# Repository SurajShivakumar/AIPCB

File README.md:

# AI PCB Copilot

Prompt an LLM to **read, review, simulate and edit KiCad projects** while you watch the changes in a browser.

It has two parts, both MCP servers, so any MCP client can use them (Claude Code, Claude Desktop, Cursor, opencode + a local model):

| Server | What it does |
|---|---|
| `kicad` | The editing engine: [mixelpixx/KiCAD-MCP-Server](https://github.com/mixelpixx/KiCAD-MCP-Server) v2.8.2 (MIT). ~240 tools: place, wire and label symbols; footprints; routing; exports; JLCPCB parts. |
| `copilot` | This repo. Checkpoints and undo, pin-level netlist diff, `verify_edit`, measured design review, SPICE on **LTspice and ngspice**, and a live browser view. |

See [PLAN.md](PLAN.md) for the design and roadmap.

## Setup (Windows)

You need KiCad 9 or 10, Node 18+, Python 3.11+ and git. LTspice is optional; ngspice comes with KiCad.

```powershell
powershell -ExecutionPolicy Bypass -File setup.ps1
```

The script clones the engine at its pinned tag, builds it against KiCad's Python, installs the copilot and runs the tests.

## Use it with Claude Code

```powershell
cd "AI PCB Generator"
claude          # approve the 'kicad' and 'copilot' servers the first time
```

Example prompts:

- *"Open workspace/fc and start the live view."*
- *"Review this board."* (uses the `review-schematic` skill)
- *"Add a 10k pull-up from nFAULT to 3.3V."* (uses `edit-schematic`: checkpoint → edit → verify → keep or undo)
- *"Simulate the BEMF dividers at 25.2 V and check the ADC pins stay under 3.3 V, on both LTspice and ngspice."* (uses `simulate`)
- *"Undo that."*

Work on copies. `sample_boards/` holds the originals; copy a board into `workspace/` and point the agent there.

### Seeing changes live

- **Browser (always):** `start_live_view` serves `http://127.0.0.1:8765`. It re-renders through `kicad-cli` within about a second of every save, circles the parts changed since the last checkpoint, and lists diffs, ERC counts, checkpoints and review findings. Clicking a finding jumps to its parts. The "Interactive" tab uses KiCanvas (alpha).
  - You can also run it without an agent: `.venv\Scripts\python -m copilot.viewer workspace\fc`
- **KiCad schematic editor:** KiCad 9/10 has no API for editing an open schematic, so the agent edits the file. `.mcp.json` turns on `KICAD_INTERACTIVE_SCHEMATIC`, which makes eeschema reload after each write. **Save your own edits before asking the agent to edit.** It will never auto-confirm a "discard changes" dialog.
- **KiCad PCB editor:** truly live (undoable) when the board is open in pcbnew with *Preferences → Plugins → Enable IPC API server* on.

## Copilot tools

| Tool | Purpose |
|---|---|
| `project_status`, `start_live_view` | Session setup |
| `checkpoint`, `list_checkpoints`, `undo`, `restore_checkpoint` | Snapshots in a shadow git repo at `<project>/.copilot/git`. This never touches your own git. |
| `netlist_diff`, `verify_edit` | Pin-level diff (name-independent), ERC new/resolved, flags parts touched outside the plan and unplanned net merges |
| `get_netlist` | Ground-truth connectivity from `kicad-cli` |
| `review_design` | ERC, optional DRC with schematic parity, netlist rules, fab-rule checks. Writes `.copilot/review.md` |
| `spice_check`, `spice_build_deck`, `spice_run`, `spice_simulators` | Decks from the schematic; LTspice / ngspice / both with a cross-check; pass/fail assertions |
| `pin_positions`, `connect_power`, `draw_wire`, `tidy_schematic` | Edits in hand-drawn style: power symbols instead of text labels; straight on-grid wires with junction dots; grid snap and text de-overlap; saves byte-identical to KiCad's own file format |

**Build + route the V2 ESC in one go** (repo root, PowerShell):

```powershell
.\autopcb_run                 # build, route, finish, stitch, clean up, DRC - live progress dashboard in this window
.\autopcb_run --skip-build    # keep the current placement, just re-route
.\autopcb_logs                # watch a run from a second window (stays open; Ctrl+C to close; --once / --log)
.\autopcb_run --docker        # same run inside the autopcb-kicad container: nothing opens on the desktop
```

Everything is also logged to `logs/autopcb.log`.

**Each run ends with design checks and a commit.** After DRC, the pipeline:
1. runs `tools/esc_checks.py`. This covers what DRC can't see:
   - switching-loop cap distance
   - charge-pump caps
   - gate-drive length
   - signals crossing a phase pour
   - vias in pads
   - ground return under the crystal/MCU
   - mounting holes
   - 3D models
2. renders every copper layer and the 3D top and bottom views into `workspace/esc_v2/review/`.
3. commits the KiCad project and the review folder to the `esc-v2` branch of [Autonomous-Flight-Team/ESC_PCB](https://github.com/Autonomous-Flight-Team/ESC_PCB), using `tools/publish_branch.py`. Pass `--no-publish` to skip the commit.

**No windows.**
- Every tool starts its child processes hidden (`tools/_quiet.py`).
- `--docker` runs the whole build and route in Linux. The image is `docker/Dockerfile`: KiCad 9.0.6, numpy, numba and Pillow. It is built on first use, and the Docker engine is started headless with `docker desktop start`.
- The image has no 3D model library, so the 3D views and the git push run on Windows afterwards, also hidden.
- KiCad paths come from `tools/_env.py`. Override them with `AUTOPCB_KPY`, `KICAD_CLI` and `KICAD_SHARE`.

**Board scripts** (`tools/`, run with KiCad's Python at `vendor/KiCAD-MCP-Server/venv/Scripts/python.exe`):

| Script | Purpose |
|---|---|
| `sync_board.py` | "Update PCB from Schematic", scripted: adds and moves footprints, reloads changed library footprints, renames nets on existing copper, locks existing routing |
| `route_board.py` | Freerouting autoroute. Plane nets are left to pours. `--keep` adds routes without touching existing ones. Picks a Java new enough for Freerouting. |
| `finish_route.py` + `maze_route.py` | Routes exactly what KiCad's ratsnest still reports missing, with a clearance-aware 2-layer maze router that respects edge and top-layer keep-outs |
| `prune_tracks.py`, `stitch_islands.py`, `silk_fix.py` | Remove dangling stubs and vias; stitch pour islands; move reference designators off pads and other silkscreen |
| `build_esc_v2.py` | Generates the 4-layer V2 ESC board: placement, stackup, zones, via fields, top-layer signal keep-out |
| `drc_summary.py`, `jlc_lookup.py` | Compact DRC report; JLCPCB/LCSC part lookup (basic/extended, stock, price) |

**Review rules:**
- Errors:
  - capacitors wired only to each other (a missing supply label)
  - missing decoupling on IC supply pins
  - USB-C CC pins without pull-downs
  - unannotated parts, missing footprints
  - schematic/PCB disagreement
  - tracks or vias below the fab's limits
- Warnings:
  - missing pull-ups on I2C / open-drain lines
  - crystals without load caps
  - LEDs without a resistor
  - look-alike net names that aren't connected
  - single-pin labelled nets
  - sheets pointing at missing files
  - symbols off the page
  - project DRC limits looser than the fab
- Fab profiles live in [fab-profiles/](fab-profiles/).

## Other clients

Point any MCP client at the same two commands. The paths are relative to this folder; use absolute paths if the client starts elsewhere.

- engine: `node vendor/KiCAD-MCP-Server/dist/index.js`
- copilot: `.venv/Scripts/python.exe -m copilot.server`

**Free / local:** [opencode](https://opencode.ai) with Ollama or LM Studio. Use a model with solid tool calling (Qwen3-Coder class or bigger); small models struggle with long edit chains. The engine ships `setup-windows-opencode.ps1` for its half.

## Tests

```powershell
.venv\Scripts\python -m pytest
```

The tests cover the netlist diff, value parsing, an RC transient on both simulators with a cross-check, and the review rules against netlists from the sample boards.

## Known limits

- **Schematic edits are file edits.** "Live" in eeschema means it reloads after each write.
- **The engine's own net listing misses power-symbol nets.** The copilot uses `kicad-cli` as ground truth.
- **The engine can report a connection as done when it isn't.** `verify_edit` catches this, which is why the edit loop always verifies.
- **SPICE models R/C/L/ferrite/diode/zener/LED automatically.** ICs need a `loads` stand-in or a `models` line.
- **DRC takes about 1 minute on a 4-layer board,** so it's opt-in.

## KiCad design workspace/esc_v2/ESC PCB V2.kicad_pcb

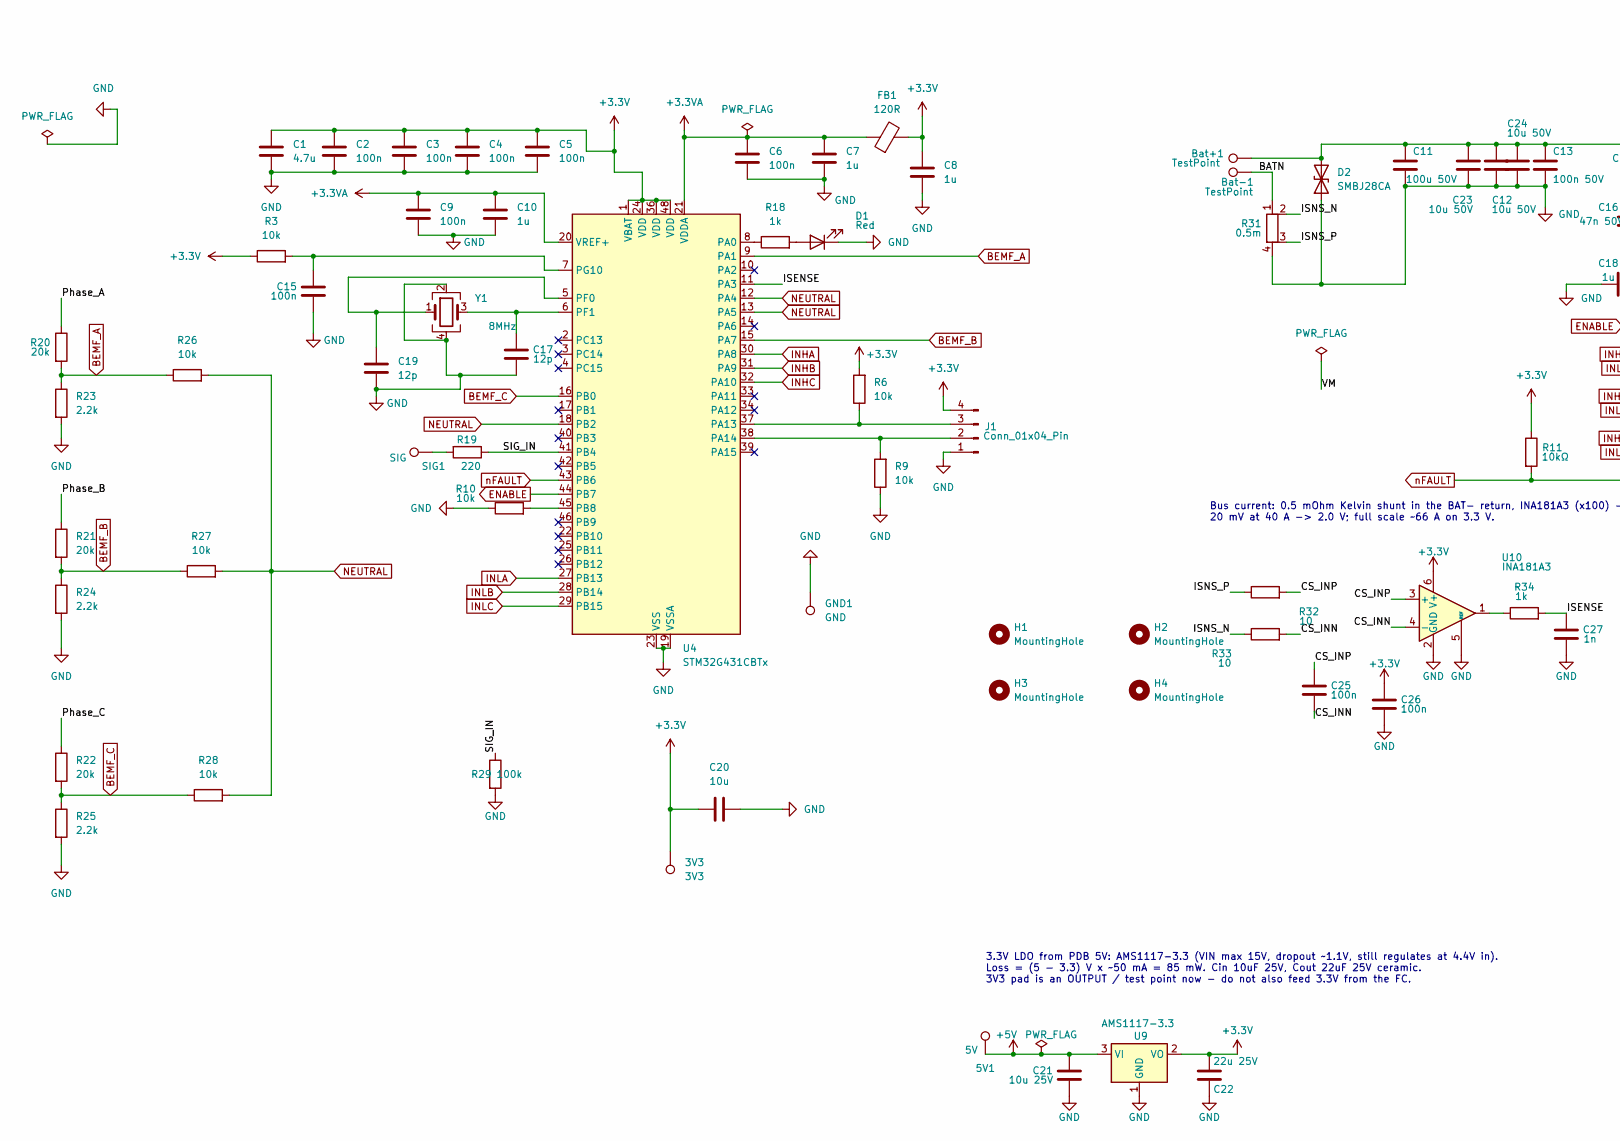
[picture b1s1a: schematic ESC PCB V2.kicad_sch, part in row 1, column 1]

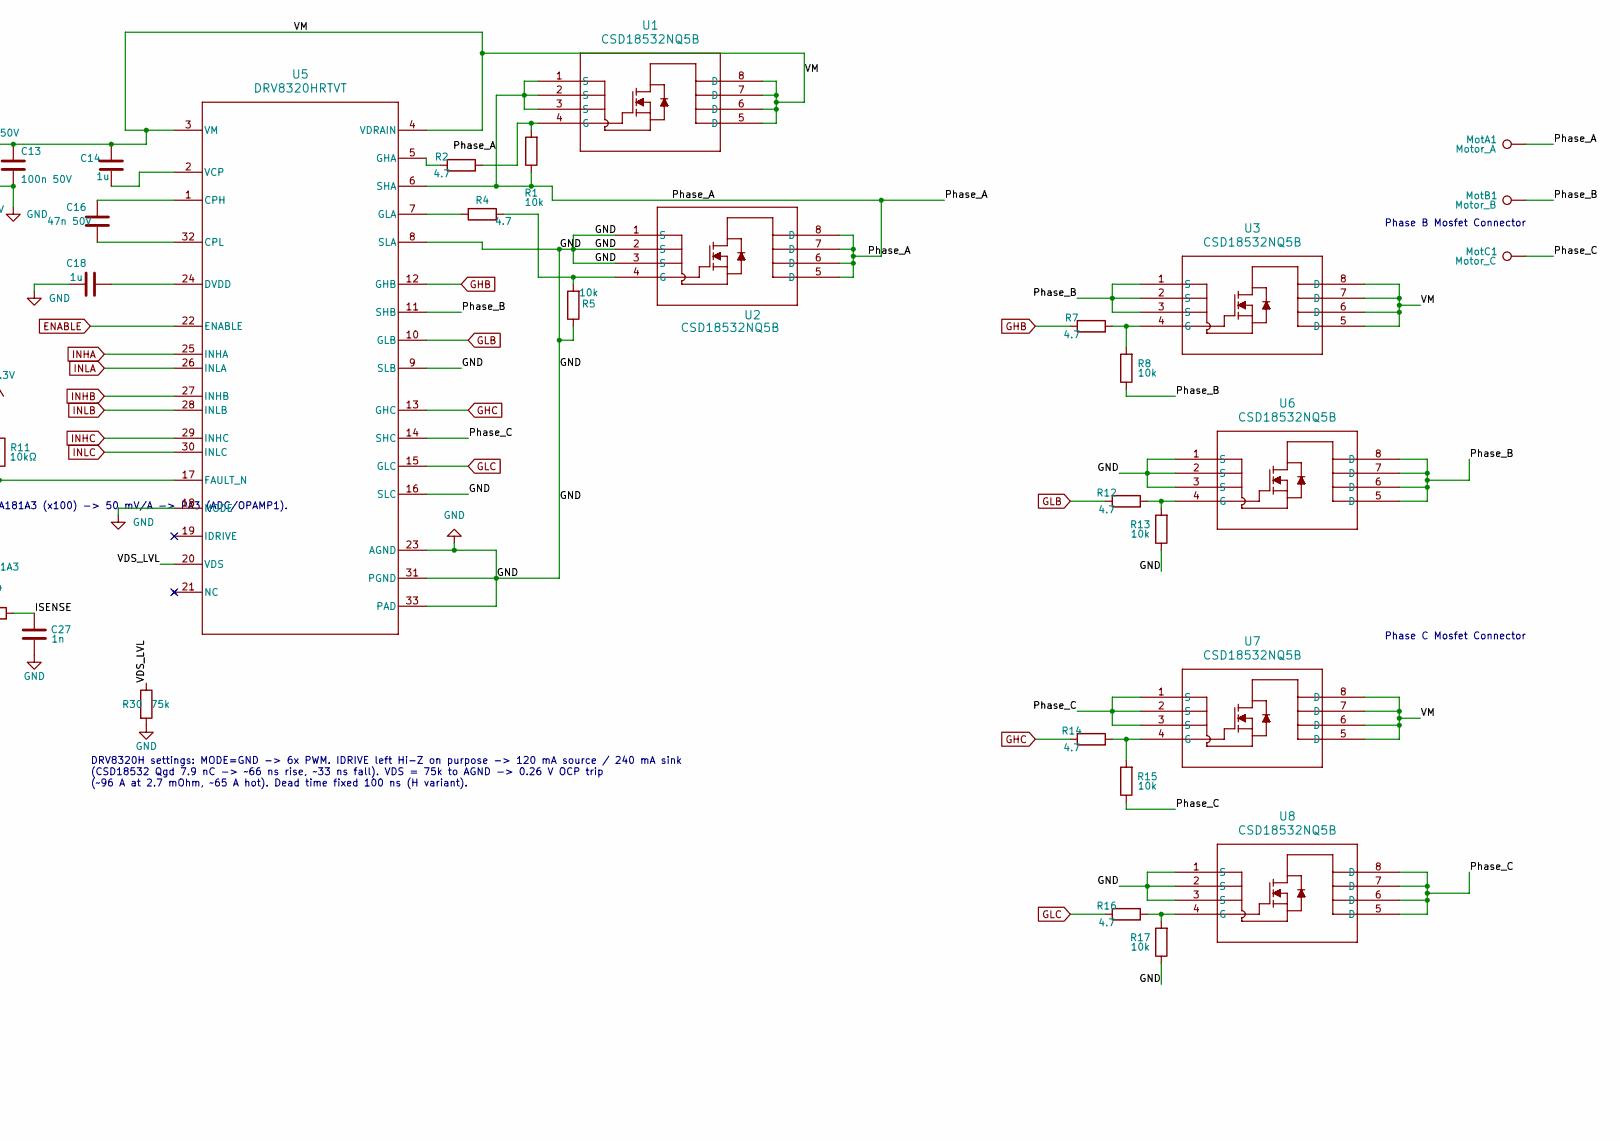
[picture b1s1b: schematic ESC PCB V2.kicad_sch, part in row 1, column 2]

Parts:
3V3: 3V3; SolderWirePad_1x01_SMD_2x4mm
5V1: 5V; SolderWirePad_1x01_SMD_2x4mm
Bat+1: TestPoint; SolderWirePad_1x01_SMD_5x10mm
Bat-1: TestPoint; SolderWirePad_1x01_SMD_5x10mm
C1: 4.7u; C_0603_1608Metric; MPN CL10A475KO8NNNC; LCSC C19666
C2, C3, C4, C5, C6, C9, C15, C25, C26: 100n; C_0603_1608Metric; MPN CC0603KRX7R9BB104; LCSC C14663
C7, C8, C10, C14, C18: 1u; C_0603_1608Metric; MPN CL10A105KB8NNNC; LCSC C15849
C11: 100u 50V; CP_Elec_10x10.5; MPN EEE-FK1H101P
C12, C23, C24: 10u 50V; C_1210_3225Metric; MPN GRM32ER61H106KA12L; LCSC C412253
C13: 100n 50V; C_0603_1608Metric; MPN CC0603KRX7R9BB104; LCSC C14663
C16: 47n 50V; C_0603_1608Metric; MPN CL10B473KB8NNNC; LCSC C1622
C17, C19: 12p; C_0603_1608Metric; MPN CL10C120JB8NNNC; LCSC C38523
C20: 10u; C_0603_1608Metric; MPN CL10A106KP8NNNC; LCSC C19702
C21: 10u 25V; C_0603_1608Metric; MPN CL10A106MA8NRNC; LCSC C96446
C22: 22u 25V; C_0805_2012Metric; MPN CL21A226MAQNNNE; LCSC C45783
C27: 1n; C_0603_1608Metric; MPN CL10B102KB8NNNC; LCSC C1588
D1: Red; LED_0603_1608Metric; MPN KT-0603R; LCSC C2286
D2: SMBJ28CA; SMBJSeries_LTF; MPN SMBJ28CA; LCSC C19077583
FB1: 120R; L_0603_1608Metric; MPN BLM18PG121SN1D; LCSC C14709
GND1: GND; SolderWirePad_1x01_SMD_2x4mm
H1, H2, H3, H4: MountingHole; MountingHole_3.2mm_M3
J1: Conn_01x04_Pin; JST_SH_SM04B-SRSS-TB_1x04-1MP_P1.00mm_Horizontal; MPN SM04B-SRSS-TB(LF)(SN); LCSC C160404
MotA1: Motor_A; SolderWirePad_1x01_SMD_5x10mm
MotB1: Motor_B; SolderWirePad_1x01_SMD_5x10mm
MotC1: Motor_C; SolderWirePad_1x01_SMD_5x10mm
R1, R3, R5, R6, R8, R9, R10, R13, R15, R17, R26, R27, R28: 10k; R_0603_1608Metric; MPN 0603WAF1002T5E; LCSC C25804
R2, R4, R7, R12, R14, R16: 4.7; R_0603_1608Metric; MPN 0603WAF470KT5E; LCSC C23164
R11: 10kΩ; R_0603_1608Metric; MPN 0603WAF1002T5E; LCSC C25804
R18, R34: 1k; R_0603_1608Metric; MPN 0603WAF1001T5E; LCSC C21190
R19: 220; R_0603_1608Metric; MPN 0603WAF2200T5E; LCSC C22962
R20, R21, R22: 20k; R_0603_1608Metric; MPN 0603WAF2002T5E; LCSC C4184
R23, R24, R25: 2.2k; R_0603_1608Metric; MPN 0603WAF2201T5E; LCSC C4190
R29: 100k; R_0603_1608Metric; MPN 0603WAF1003T5E; LCSC C25803
R30: 75k; R_0603_1608Metric; MPN 0603WAF7502T5E; LCSC C23242
R31: 0.5m; R_Shunt_2512_Kelvin; MPN RLM25FEGMR50M; LCSC C710260
R32, R33: 10; R_0603_1608Metric; MPN 0603WAF100JT5E; LCSC C22859
SIG1: SIG; SolderWirePad_1x01_SMD_2x4mm
U1, U2, U3, U6, U7, U8: CSD18532NQ5B; DNK8_TEX; MPN CSD18532NQ5B
U4: STM32G431CBTx; LQFP-48_7x7mm_P0.5mm; MPN STM32G431CBT6; LCSC C529355
U5: DRV8320HRTVT; RTV0032E; MPN DRV8320HRTVR; LCSC C701782
U9: AMS1117-3.3; SOT-223-3_TabPin2; MPN AMS1117-3.3; LCSC C6186
U10: INA181A3; SOT-23-6; MPN INA181A3IDBVR; LCSC C2652255
Y1: 8MHz; Crystal_SMD_3225-4Pin_3.2x2.5mm; MPN TAXM8M4RDBCCT2T; LCSC C400090

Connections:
+3.3V: 3V3.1, C1.1, C2.1, C3.1, C4.1, C5.1, C8.1, C20.1, C22.1, C26.1, FB1.2, J1.4, R3.1, R6.2, R11.1, U4.1 (VBAT), U4.24 (VDD), U4.36 (VDD), U4.48 (VDD), U9.2 (VO), U10.6 (V+)
+3.3VA: C6.1, C7.1, C9.1, C10.1, FB1.1, U4.20 (VREF+), U4.21 (VDDA)
+5V: 5V1.1, C21.1, U9.3 (VI)
/BATN: Bat-1.1, R31.1
/CS_INN: C25.2, R33.2, U10.4 (-)
/CS_INP: C25.1, R32.2, U10.3 (+)
/ISENSE: C27.1, R34.2, U4.11 (PA3)
/ISNS_N: R31.2, R33.1
/ISNS_P: R31.3, R32.1
/Phase_A: MotA1.1, R1.1, R20.1, U1.1 (S), U1.2 (S), U1.3 (S), U2.5 (D), U2.6 (D), U2.7 (D), U2.8 (D), U5.6 (SHA)
/Phase_B: MotB1.1, R8.1, R21.1, U3.1 (S), U3.2 (S), U3.3 (S), U5.11 (SHB), U6.5 (D), U6.6 (D), U6.7 (D), U6.8 (D)
/Phase_C: MotC1.1, R15.1, R22.1, U5.14 (SHC), U7.1 (S), U7.2 (S), U7.3 (S), U8.5 (D), U8.6 (D), U8.7 (D), U8.8 (D)
/SIG_IN: R19.1, R29.1, U4.41 (PB4)
/VDS_LVL: R30.1, U5.20 (VDS)
/VM: Bat+1.1, C11.1, C12.1, C13.1, C14.2, C23.1, C24.1, D2.2 (A2), U1.5 (D), U1.6 (D), U1.7 (D), U1.8 (D), U3.5 (D), U3.6 (D), U3.7 (D), U3.8 (D), U5.3 (VM), U5.4 (VDRAIN), U7.5 (D), U7.6 (D), U7.7 (D), U7.8 (D)
BEMF_A: R20.2, R23.1, R26.1, U4.9 (PA1)
BEMF_B: R21.2, R24.1, R27.1, U4.15 (PA7)
BEMF_C: R22.2, R25.1, R28.1, U4.16 (PB0)
ENABLE: U4.44 (PB7), U5.22 (ENABLE)
GHB: R7.1, U5.12 (GHB)
GHC: R14.1, U5.13 (GHC)
GLB: R12.1, U5.10 (GLB)
GLC: R16.1, U5.15 (GLC)
GND: C1.2, C2.2, C3.2, C4.2, C5.2, C6.2, C7.2, C8.2, C9.2, C10.2, C11.2, C12.2, C13.2, C15.2, C17.2, C18.1, C19.2, C20.2, C21.2, C22.2, C23.2, C24.2, C26.2, C27.2, D1.1 (K), D2.1 (A1), GND1.1, J1.1, R5.1, R9.1, R10.1, R13.1, R17.1, R23.2, R24.2, R25.2, R29.2, R30.2, R31.4, U2.1 (S), U2.2 (S), U2.3 (S), U4.19 (VSSA), U4.23 (VSS), U4.35 (VSS), U4.47 (VSS), U5.8 (SLA), U5.9 (SLB), U5.16 (SLC), U5.18 (MODE), U5.23 (AGND), U5.31 (PGND), U5.33 (PAD), U6.1 (S), U6.2 (S), U6.3 (S), U8.1 (S), U8.2 (S), U8.3 (S), U9.1 (GND), U10.2 (GND), U10.5 (REF), Y1.2, Y1.4
INHA: U4.30 (PA8), U5.25 (INHA)
INHB: U4.31 (PA9), U5.27 (INHB)
INHC: U4.32 (PA10), U5.29 (INHC)
INLA: U4.27 (PB13), U5.26 (INLA)
INLB: U4.28 (PB14), U5.28 (INLB)
INLC: U4.29 (PB15), U5.30 (INLC)
NEUTRAL: R26.2, R27.2, R28.2, U4.12 (PA4), U4.13 (PA5), U4.18 (PB2)
unnamed: D1.2 (A), R18.2
unnamed: J1.2, R9.2, U4.38 (PA14)
unnamed: J1.3, R6.1, U4.37 (PA13)
unnamed: R19.2, SIG1.1
unnamed: R34.1, U10.1
unnamed: R1.2, R2.2, U1.4 (G)
unnamed: R4.2, R5.2, U2.4 (G)
unnamed: R7.2, R8.2, U3.4 (G)
unnamed: R18.1, U4.8 (PA0)
unnamed: R10.2, U4.45 (PB8)
unnamed: C19.1, U4.5 (PF0), Y1.1
unnamed: C17.1, U4.6 (PF1), Y1.3
unnamed: C15.1, R3.2, U4.7 (PG10)
unnamed: C16.2, U5.1 (CPH)
unnamed: C16.1, U5.32 (CPL)
unnamed: C18.2, U5.24 (DVDD)
unnamed: R2.1, U5.5 (GHA)
unnamed: R4.1, U5.7 (GLA)
unnamed: C14.1, U5.2 (VCP)
unnamed: R12.2, R13.2, U6.4 (G)
unnamed: R14.2, R15.2, U7.4 (G)
unnamed: R16.2, R17.2, U8.4 (G)
nFAULT: R11.2, U4.43 (PB6), U5.17 (FAULT_N)

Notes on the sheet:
3.3V LDO from PDB 5V: AMS1117-3.3 (VIN max 15V, dropout ~1.1V, still regulates at 4.4V in). Loss = (5 - 3.3) V x ~50 mA = 85 mW. Cin 10uF 25V, Cout 22uF 25V ceramic. 3V3 pad is an OUTPUT / test point now - do not also feed 3.3V from the FC.
DRV8320H settings: MODE=GND -> 6x PWM. IDRIVE left Hi-Z on purpose -> 120 mA source / 240 mA sink (CSD18532 Qgd 7.9 nC -> ~66 ns rise, ~33 ns fall). VDS = 75k to AGND -> 0.26 V OCP trip (~96 A at 2.7 mOhm, ~65 A hot). Dead time fixed 100 ns (H variant).
Phase C Mosfet Connector
Phase B Mosfet Connector
Bus current: 0.5 mOhm Kelvin shunt in the BAT- return, INA181A3 (x100) -> 50 mV/A -> PA3 (ADC/OPAMP1). 20 mV at 40 A -> 2.0 V; full scale ~66 A on 3.3 V.

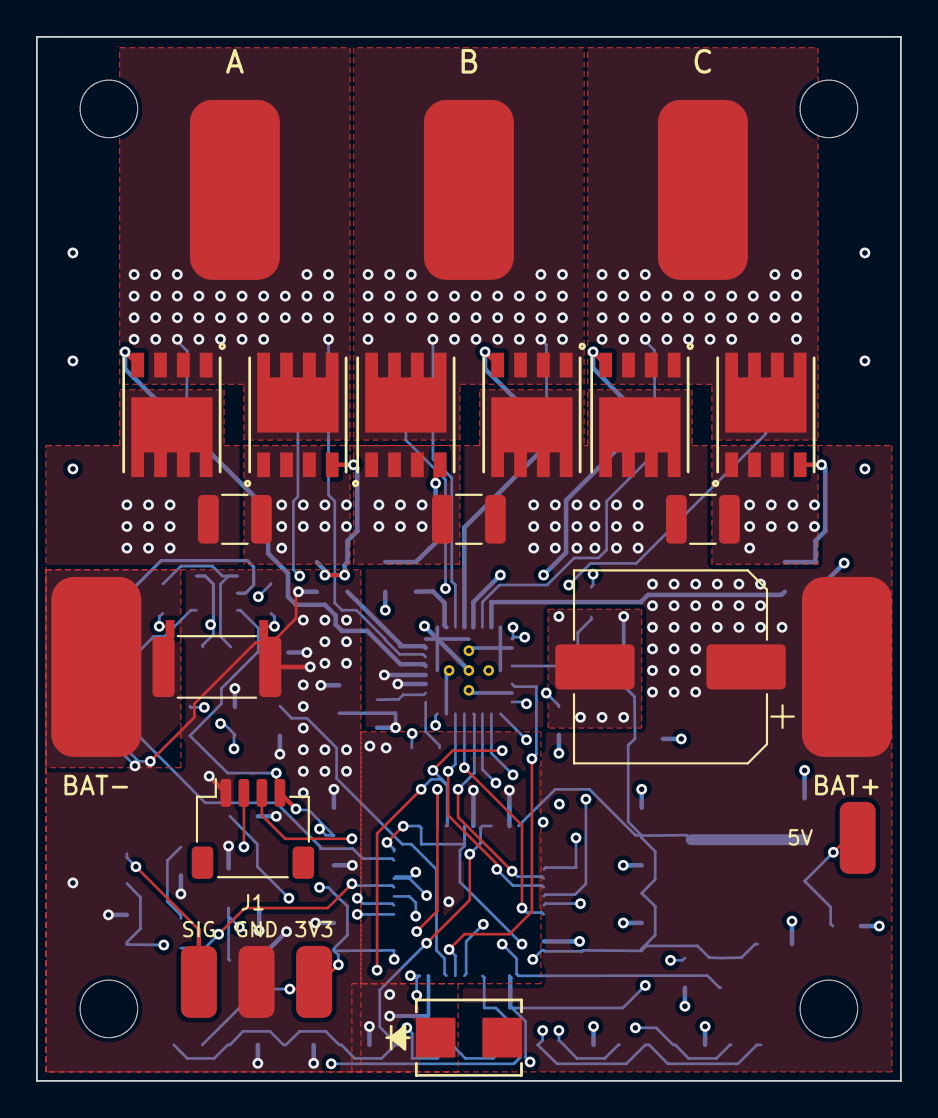
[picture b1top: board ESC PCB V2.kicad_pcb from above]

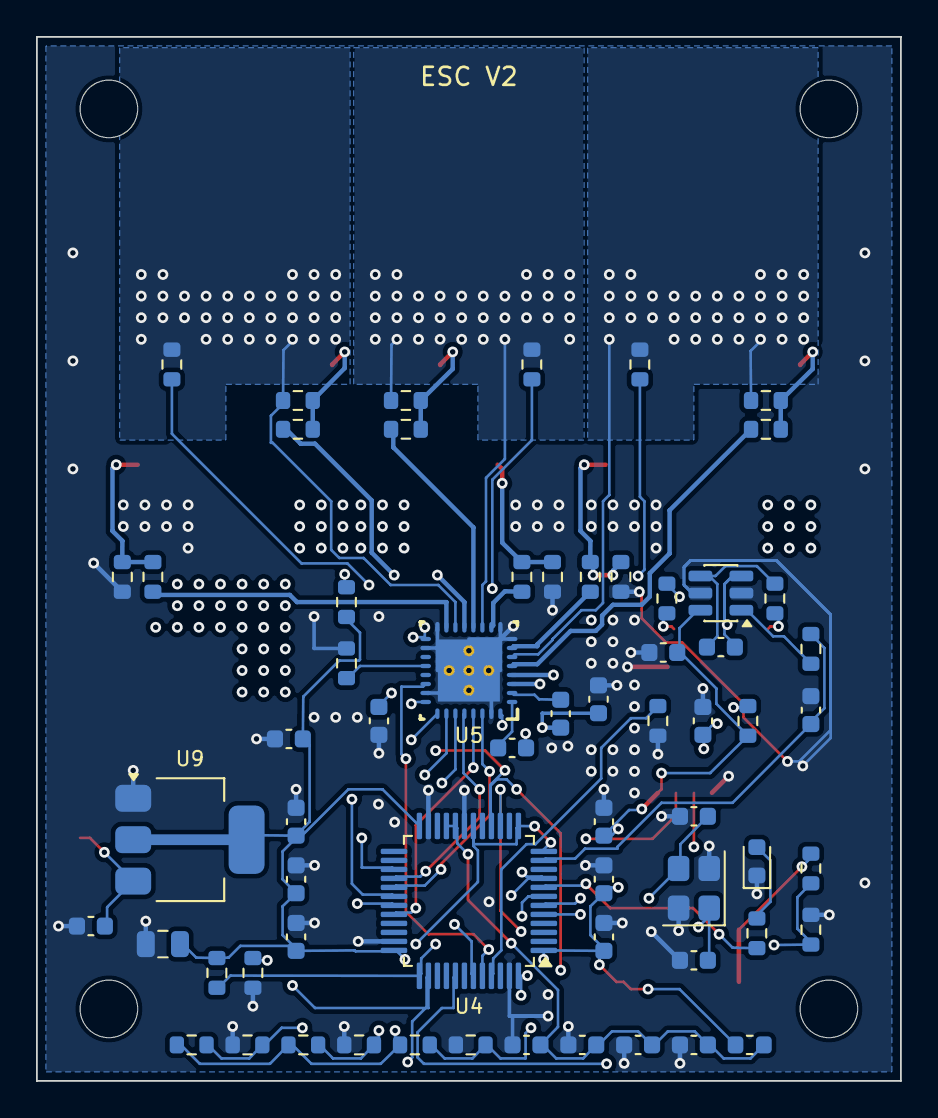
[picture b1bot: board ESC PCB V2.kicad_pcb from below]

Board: 4 copper layers, 48.0 x 58.0 mm, 89 parts (63 on the bottom side), 54 nets.

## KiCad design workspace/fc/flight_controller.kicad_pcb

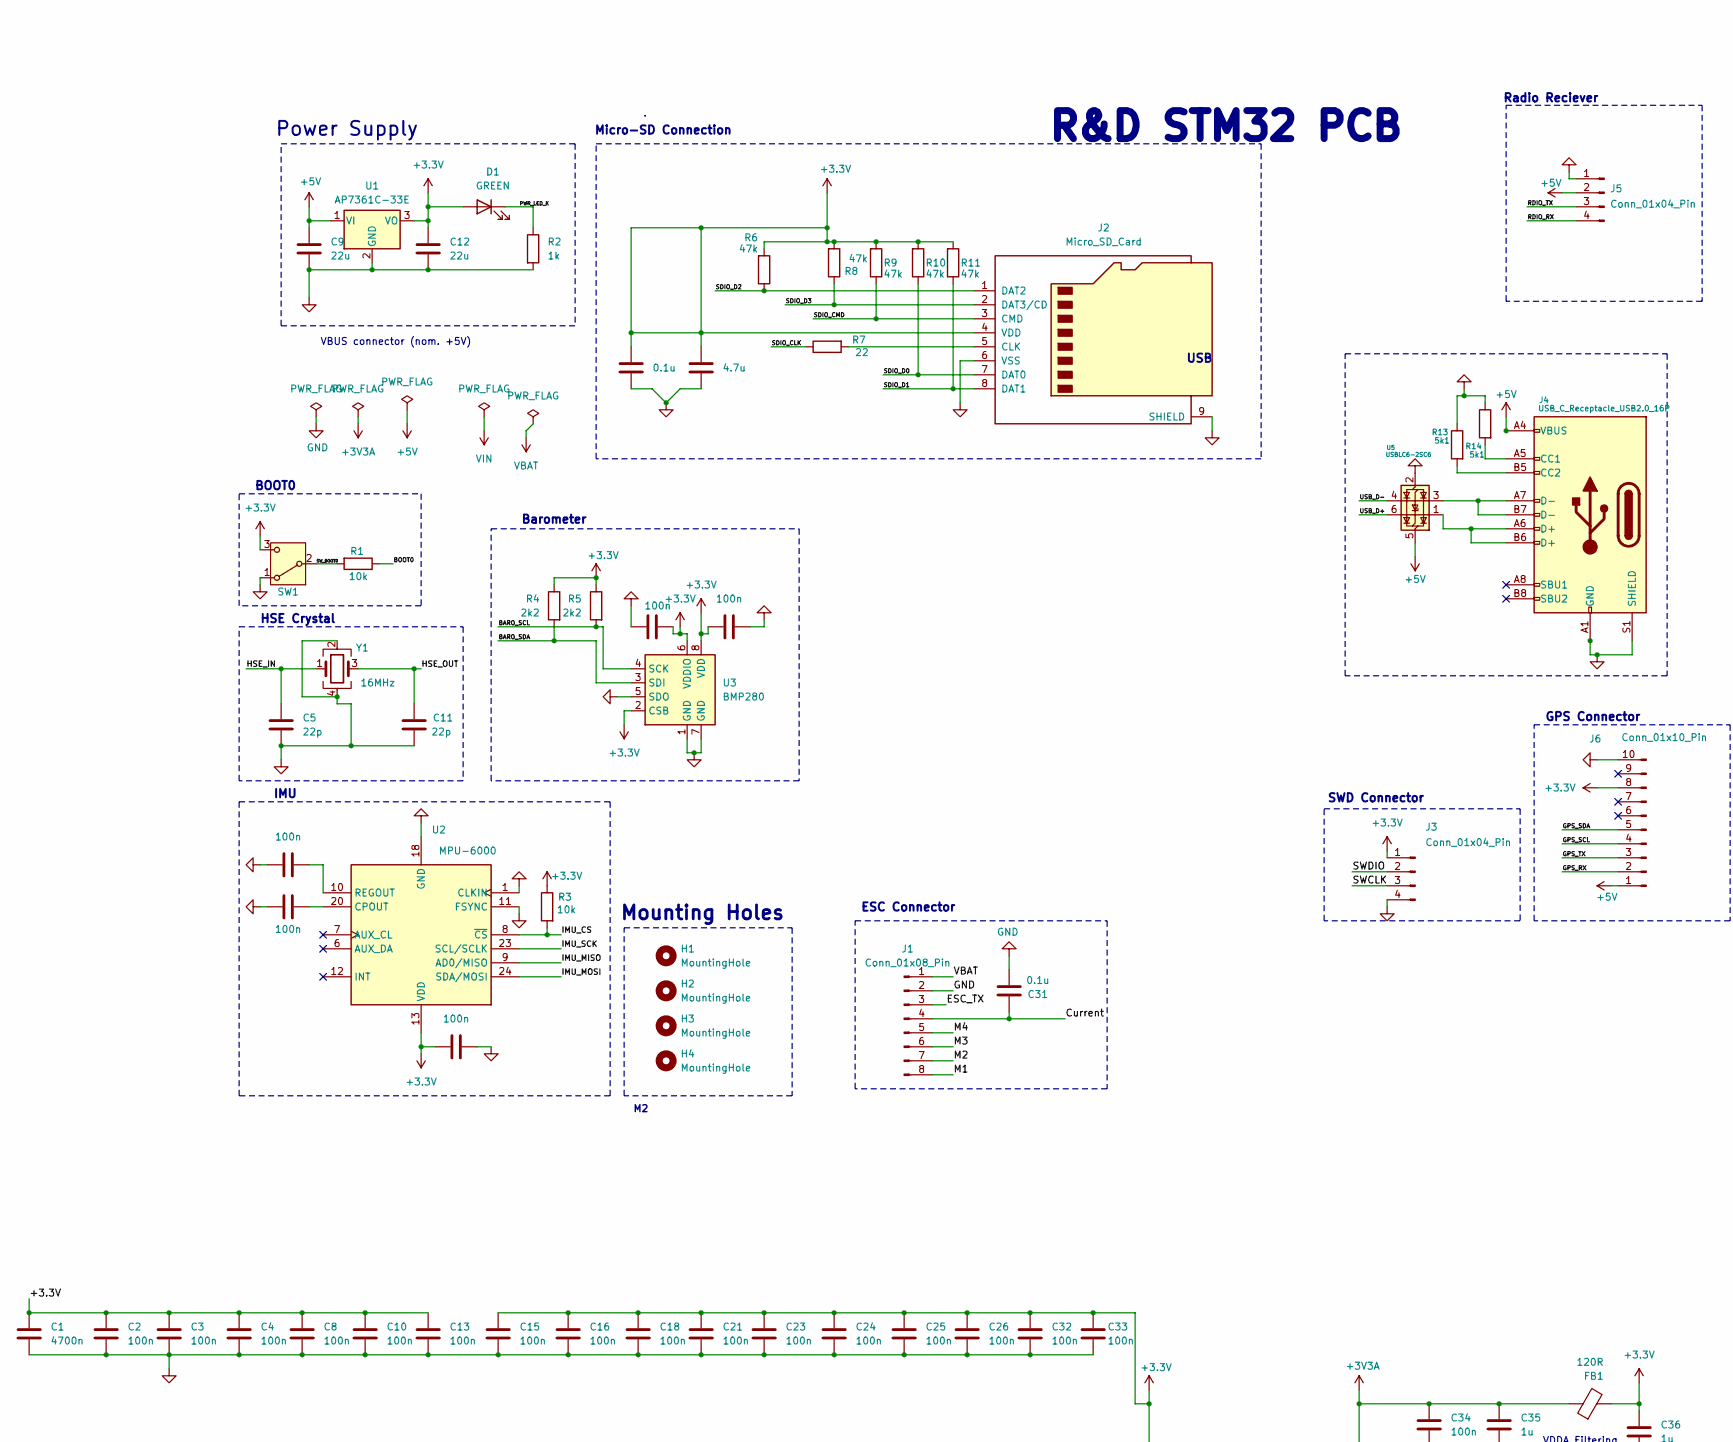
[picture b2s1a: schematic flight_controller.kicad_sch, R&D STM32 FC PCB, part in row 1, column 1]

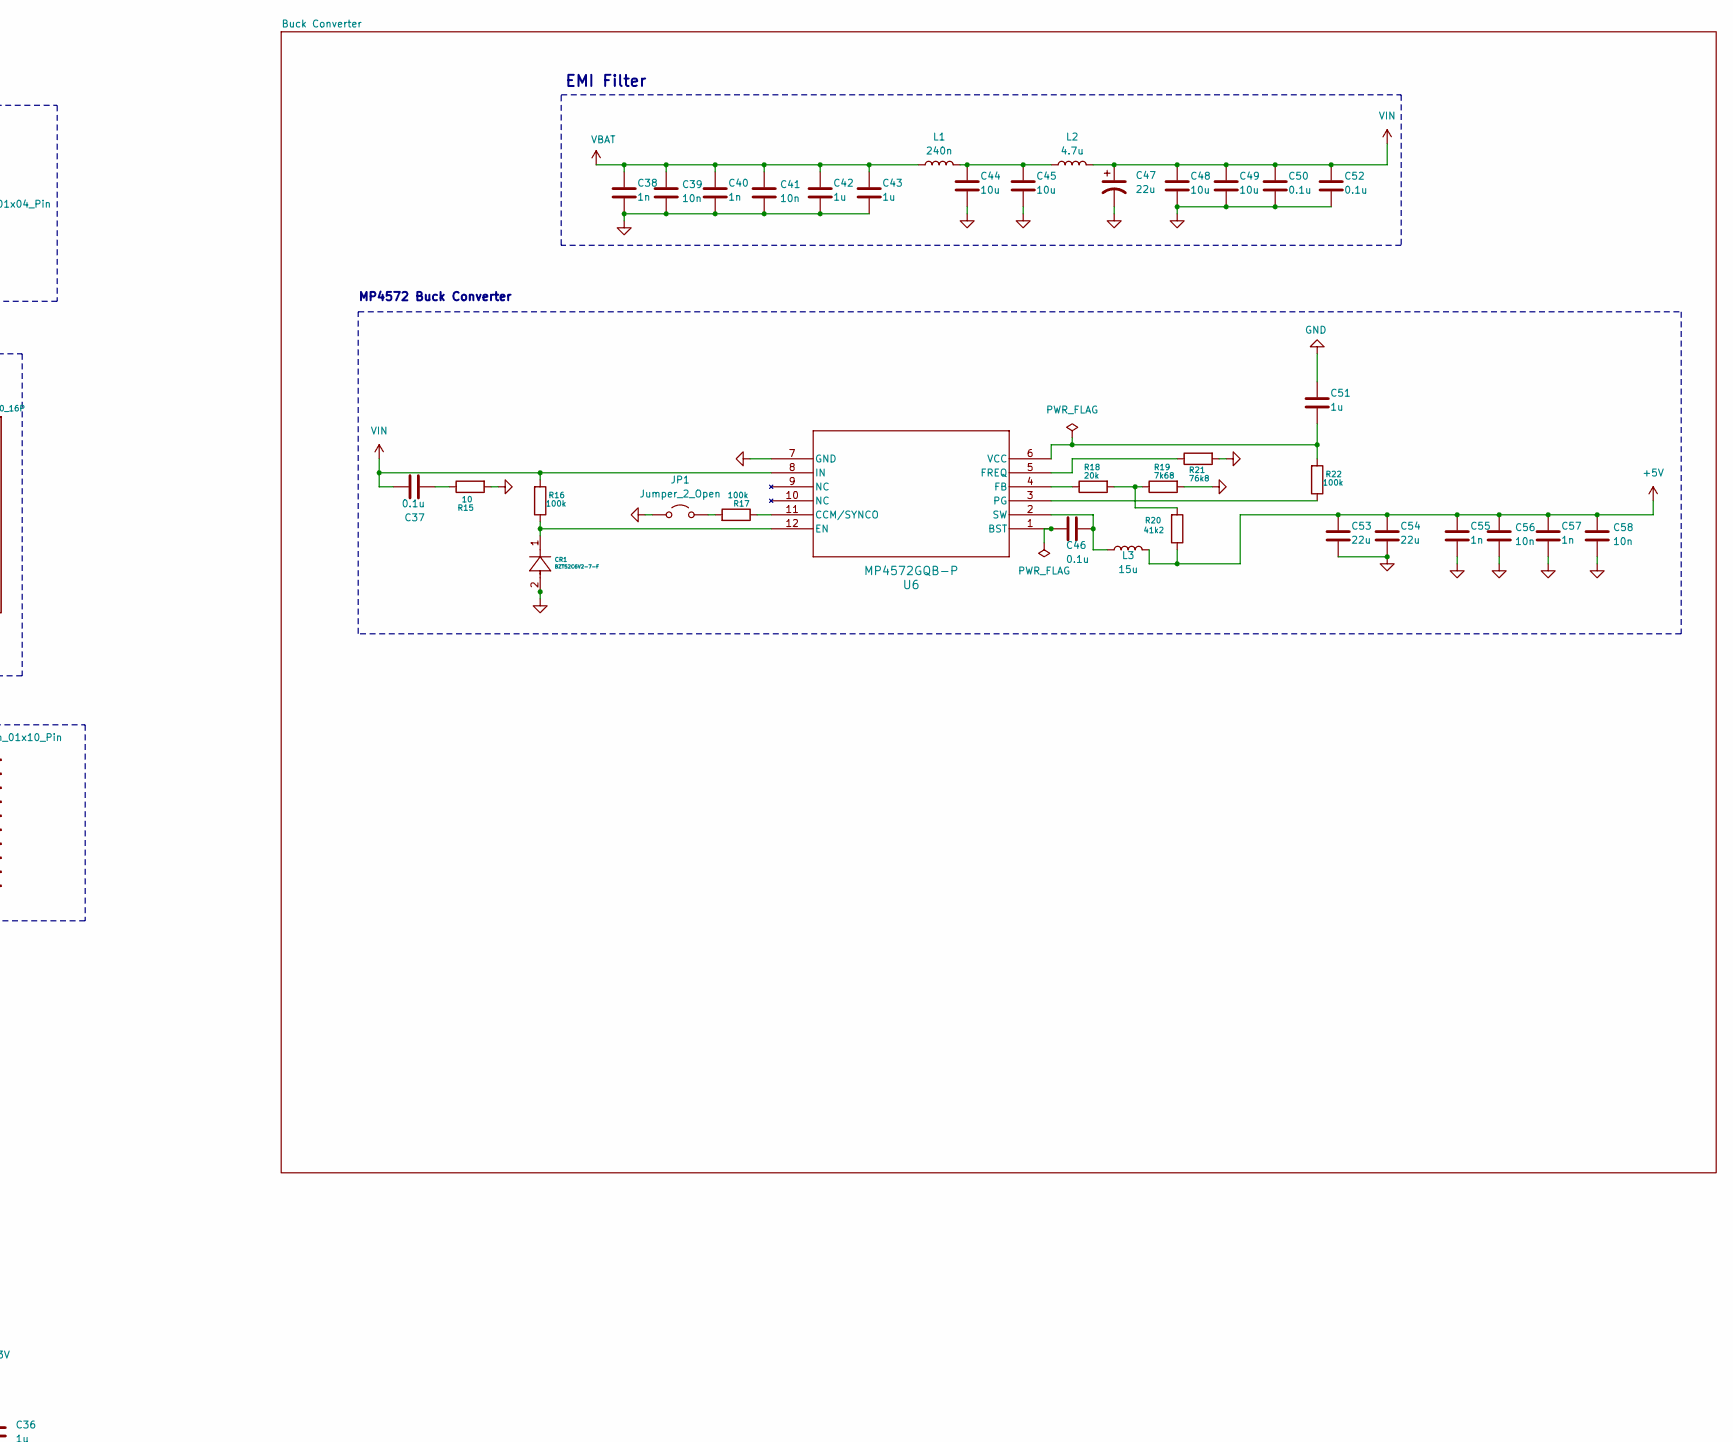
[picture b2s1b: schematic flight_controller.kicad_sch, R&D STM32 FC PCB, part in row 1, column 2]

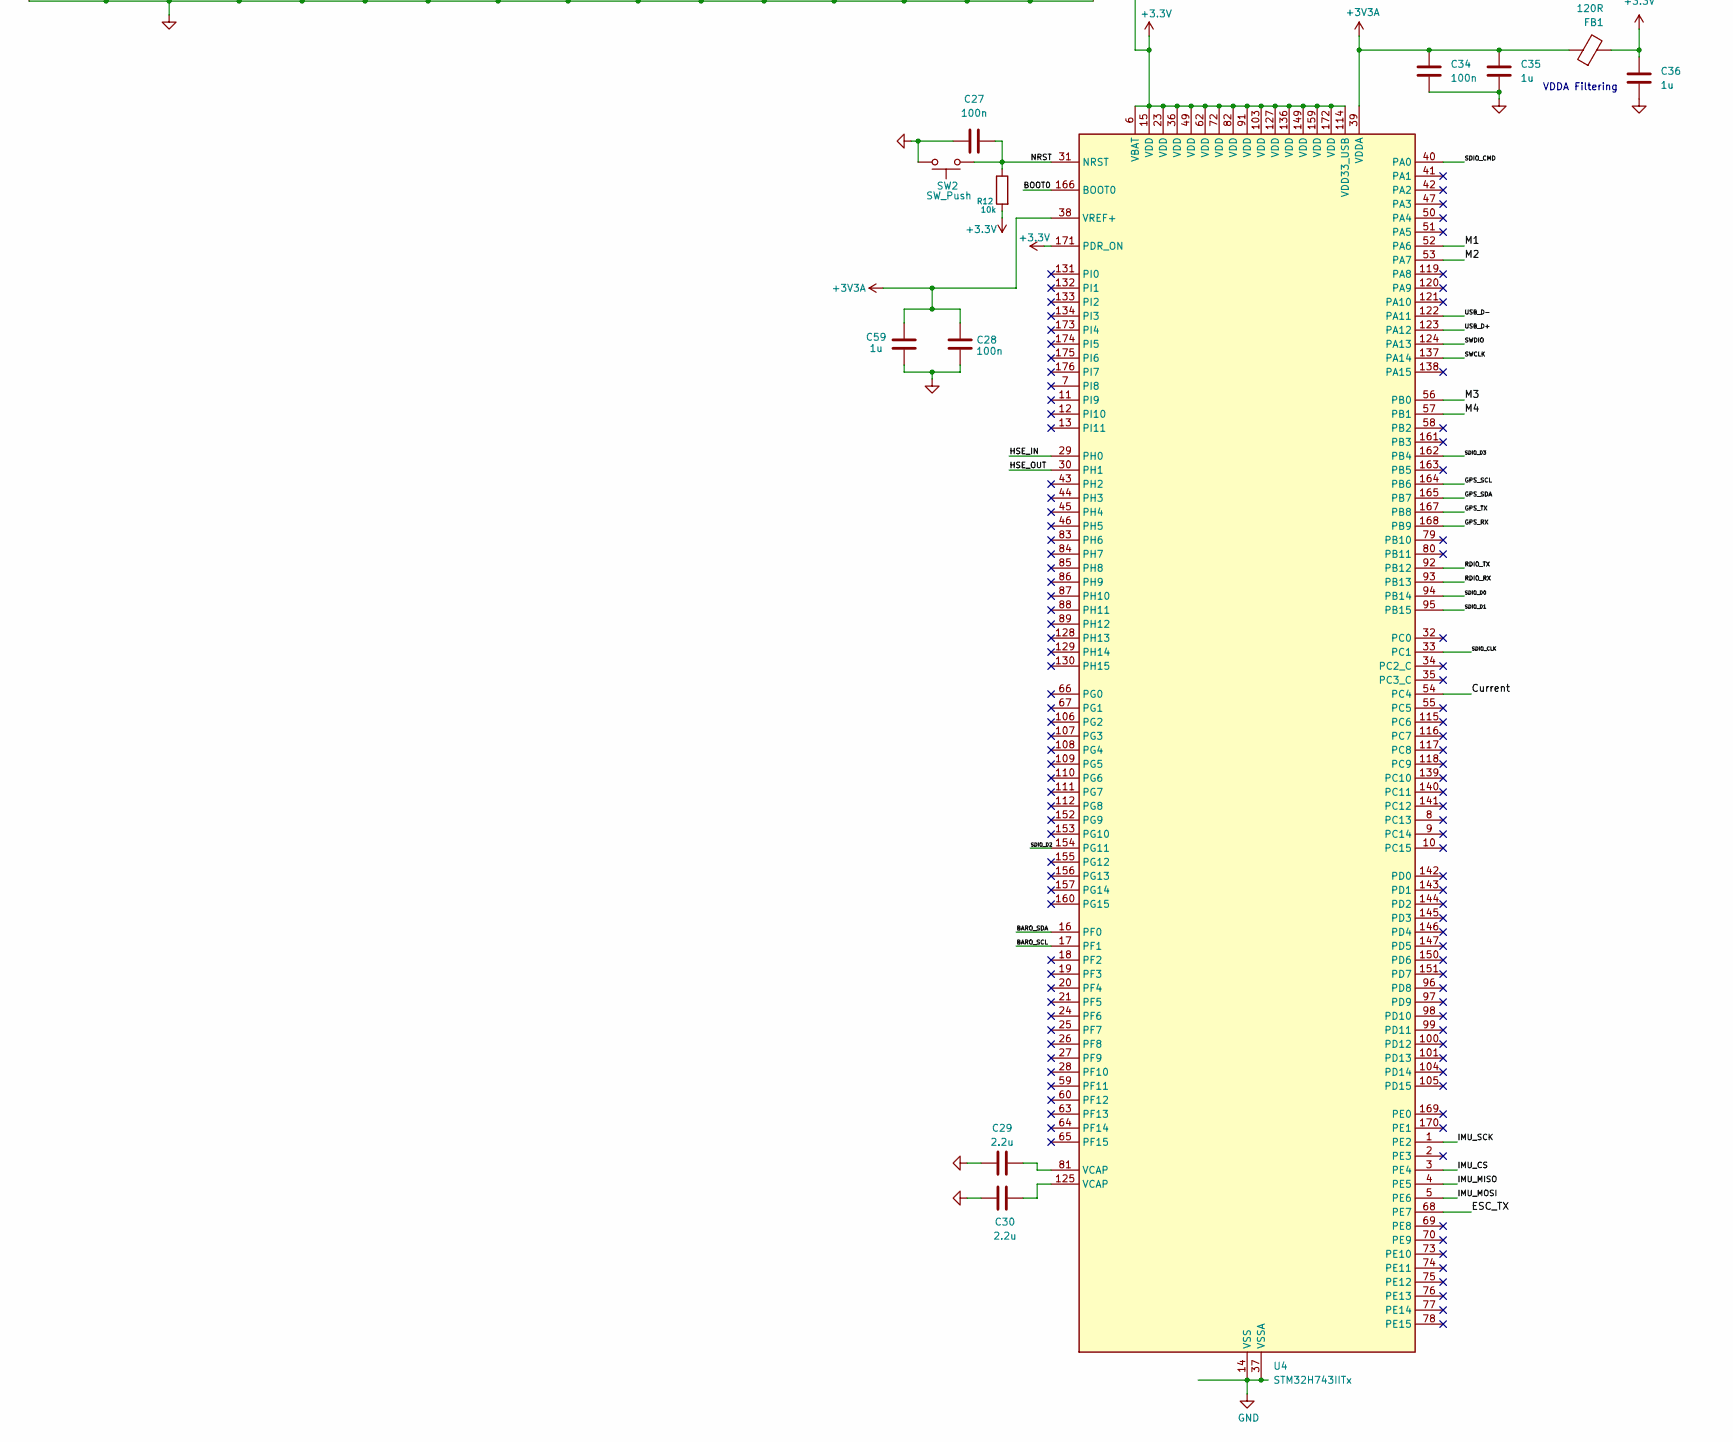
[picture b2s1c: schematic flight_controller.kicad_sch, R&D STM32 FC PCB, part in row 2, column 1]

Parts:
C1: 4700n; C_0603_1608Metric
C2, C3, C4, C6, C7, C8, C10, C13, C14, C15, C16, C18, C19, C21, C22, C23, C24, C25, C26, C27, C28, C32, C33, C34: 100n; C_0402_1005Metric
C5, C11: 22p; C_0402_1005Metric
C9, C12: 22u; C_0805_2012Metric
C17, C31, C37, C46, C50, C52: 0.1u; C_0402_1005Metric
C20: 4.7u; C_0402_1005Metric
C29, C30: 2.2u; C_0402_1005Metric
C35, C36, C42, C43, C51, C59: 1u; C_0402_1005Metric
C38, C40, C55, C57: 1n; C_0402_1005Metric
C39, C41, C56, C58: 10n; C_0402_1005Metric
C44, C45, C48, C49: 10u; C_0402_1005Metric
C47, C53, C54: 22u; C_0402_1005Metric
CR1: BZT52C6V2-7-F; D_SOD-123
D1: GREEN; LED_0603_1608Metric
FB1: 120R; L_0603_1608Metric
H1, H2, H3, H4: MountingHole; MountingHole_2.2mm_M2
J1: Conn_01x08_Pin; JST_GH_BM08B-GHS-TBT_1x08-1MP_P1.25mm_Vertical
J2: Micro_SD_Card; microSD_HC_Wuerth_693072010801
J3, J5: Conn_01x04_Pin; PinHeader_1x04_P2.54mm_Vertical
J4: USB_C_Receptacle_USB2.0_16P; USB_C_Receptacle_HRO_TYPE-C-31-M-12
J6: Conn_01x10_Pin; JST_GH_BM10B-GHS-TBT_1x10-1MP_P1.25mm_Vertical
JP1: Jumper_2_Open; SolderJumper-2_P1.3mm_Open_Pad1.0x1.5mm
L1: 240n; L_0603_1608Metric
L2: 4.7u; L_Bourns-SRN4018
L3: 15u; L_Bourns-SRN4018
R1, R3, R12: 10k; R_0402_1005Metric
R2: 1k; R_0402_1005Metric
R4, R5: 2k2; R_0402_1005Metric
R6, R8, R9, R10, R11: 47k; R_0402_1005Metric
R7: 22; R_0402_1005Metric
R13, R14: 5k1; R_0402_1005Metric
R15: 10; R_0402_1005Metric
R16, R17, R22: 100k; R_0402_1005Metric
R18: 20k; R_0402_1005Metric
R19: 7k68; R_0402_1005Metric
R20: 41k2; R_0402_1005Metric
R21: 76k8; R_0402_1005Metric
SW1: SW_SPDT; SW_SPDT_PCM12
SW2: SW_Push; SW_SPST_TL3342
U1: AP7361C-33E; SOT-223-3_TabPin2
U2: MPU-6000; InvenSense_QFN-24_4x4mm_P0.5mm
U3: BMP280; Bosch_LGA-8_2x2.5mm_P0.65mm_ClockwisePinNumbering
U4: STM32H743IITx; LQFP-176_24x24mm_P0.5mm
U5: USBLC6-2SC6; SOT-23-6
U6: MP4572GQB-P; QFN-12_MPQ4572-AEC1_MNP
Y1: 16MHz; Crystal_SMD_3225-4Pin_3.2x2.5mm

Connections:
+3.3V: C1.1, C2.1, C3.1, C4.1, C8.1, C10.1, C12.1, C13.1, C14.2, C15.1, C16.1, C17.1, C18.1, C19.1, C20.1, C21.1, C22.2, C23.1, C24.1, C25.1, C26.1, C32.1, C33.1, C36.1, D1.2 (A), FB1.2, J2.4 (VDD), J3.1, J6.8, R3.1, R4.1, R5.1, R6.2, R8.2, R9.2, R10.2, R11.2, R12.2, SW1.3 (C), U1.3 (VO), U2.13 (VDD), U3.2 (CSB), U3.6 (VDDIO), U3.8 (VDD), U4.6 (VBAT), U4.15 (VDD), U4.23 (VDD), U4.36 (VDD), U4.49 (VDD), U4.62 (VDD), U4.72 (VDD), U4.82 (VDD), U4.91 (VDD), U4.103 (VDD), U4.114 (VDD33_USB), U4.127 (VDD), U4.136 (VDD), U4.149 (VDD), U4.159 (VDD), U4.171 (PDR_ON), U4.172 (VDD)
+3V3A: C28.2, C34.1, C35.1, C59.2, FB1.1, U4.38 (VREF+), U4.39 (VDDA)
+5V: C9.1, C53.1, C54.1, C55.1, C56.1, C57.1, C58.1, J4.A4 (VBUS), J4.A9 (VBUS), J4.B4 (VBUS), J4.B9 (VBUS), J5.2, J6.1, L3.2, R20.1, U1.1 (VI), U5.5 (VBUS)
/BARO_SCL: R5.2, U3.4 (SCK), U4.17 (PF1)
/BARO_SDA: R4.2, U3.3 (SDI), U4.16 (PF0)
/BOOT0: R1.1, U4.166 (BOOT0)
/Current: C31.1, J1.4, U4.54 (PC4)
/ESC_TX: J1.3, U4.68 (PE7)
/GPS_RX: J6.2, U4.168 (PB9)
/GPS_SCL: J6.4, U4.164 (PB6)
/GPS_SDA: J6.5, U4.165 (PB7)
/GPS_TX: J6.3, U4.167 (PB8)
/HSE_IN: C5.1, U4.29 (PH0), Y1.1
/HSE_OUT: C11.1, U4.30 (PH1), Y1.3
/IMU_CS: R3.2, U2.8 (~CS), U4.3 (PE4)
/IMU_MISO: U2.9 (AD0/MISO), U4.4 (PE5)
/IMU_MOSI: U2.24 (SDA/MOSI), U4.5 (PE6)
/IMU_SCK: U2.23 (SCL/SCLK), U4.1 (PE2)
/M1: J1.8, U4.52 (PA6)
/M2: J1.7, U4.53 (PA7)
/M3: J1.6, U4.56 (PB0)
/M4: J1.5, U4.57 (PB1)
/NRST: C27.2, R12.1, SW2.1, U4.31 (NRST)
/PWR_LED_K: D1.1 (K), R2.1
/RDIO_RX: J5.4, U4.93 (PB13)
/RDIO_TX: J5.3, U4.92 (PB12)
/SDIO_CLK: R7.1, U4.33 (PC1)
/SDIO_CMD: J2.3 (CMD), R9.1, U4.40 (PA0)
/SDIO_D0: J2.7 (DAT0), R10.1, U4.94 (PB14)
/SDIO_D1: J2.8 (DAT1), R11.1, U4.95 (PB15)
/SDIO_D2: J2.1 (DAT2), R6.1, U4.154 (PG11)
/SDIO_D3: J2.2 (DAT3/CD), R8.1, U4.162 (PB4)
/SWCLK: J3.3, U4.137 (PA14)
/SWDIO: J3.2, U4.124 (PA13)
/SW_BOOT0: R1.2, SW1.2 (B)
/USB_D+: U4.123 (PA12), U5.6 (I/O1)
/USB_D-: U4.122 (PA11), U5.4 (I/O2)
GND: C1.2, C2.2, C3.2, C4.2, C5.2, C6.1, C7.1, C8.2, C9.2, C10.2, C11.2, C12.2, C13.2, C14.1, C15.2, C16.2, C17.2, C18.2, C19.2, C20.2, C21.2, C22.1, C23.2, C24.2, C25.2, C26.2, C27.1, C28.1, C29.1, C30.1, C31.2, C32.2, C33.2, C34.2, C35.2, C36.2, C38.2, C39.2, C40.2, C41.2, C42.2, C43.2, C44.2, C45.2, C47.2, C48.2, C49.2, C50.2, C51.1, C52.2, C53.2, C54.2, C55.2, C56.2, C57.2, C58.2, C59.1, CR1.2, J1.2, J2.6 (VSS), J2.9 (SHIELD), J3.4, J4.A1 (GND), J4.A12 (GND), J4.B1 (GND), J4.B12 (GND), J4.S1 (SHIELD), J5.1, J6.10, JP1.1 (A), R2.2, R13.1, R14.1, R15.2, R19.2, R21.2, SW1.1 (A), SW2.2, U1.2 (GND), U2.1 (CLKIN), U2.11 (FSYNC), U2.18 (GND), U3.1 (GND), U3.5 (SDO), U3.7 (GND), U4.14 (VSS), U4.22 (VSS), U4.37 (VSSA), U4.48 (VSS), U4.61 (VSS), U4.71 (VSS), U4.90 (VSS), U4.102 (VSS), U4.113 (VSS), U4.126 (VSS), U4.135 (VSS), U4.148 (VSS), U4.158 (VSS), U5.2 (GND), U6.7 (GND), Y1.2, Y1.4
unnamed: C29.2, U4.81 (VCAP)
unnamed: C30.2, U4.125 (VCAP)
unnamed: C37.2, R15.1
unnamed: C44.1, C45.1, L1.2, L2.1
unnamed: J2.5 (CLK), R7.2
unnamed: J4.A5 (CC1), R14.2
unnamed: J4.B5 (CC2), R13.2
unnamed: J4.A6 (D+), J4.B6 (D+), U5.1 (I/O1)
unnamed: J4.A7 (D-), J4.B7 (D-), U5.3 (I/O2)
unnamed: JP1.2 (B), R17.2
unnamed: R18.2, R19.1, R20.2
unnamed: C7.2, U2.20 (CPOUT)
unnamed: C6.2, U2.10 (REGOUT)
unnamed: C46.2, U6.1 (BST)
unnamed: R17.1, U6.11 (CCM/SYNCO)
unnamed: CR1.1, R16.1, U6.12 (EN)
unnamed: R18.1, U6.4 (FB)
unnamed: R21.1, U6.5 (FREQ)
unnamed: R22.1, U6.3 (PG)
unnamed: C46.1, L3.1, U6.2 (SW)
unnamed: C51.2, R22.2, U6.6 (VCC)
VBAT: C38.1, C39.1, C40.1, C41.1, C42.1, C43.1, J1.1, L1.1
VIN: C37.1, C47.1, C48.1, C49.1, C50.1, C52.1, L2.2, R16.2, U6.8 (IN)

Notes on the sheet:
Micro-SD Connection
MP4572 Buck Converter
USB
SWD Connector
VBUS connector (nom. +5V)
VDDA Filtering
Barometer
Mounting Holes
IMU
HSE Crystal
ESC Connector
BOOT0
Power Supply
EMI Filter
GPS Connector
Radio Reciever
R&D STM32 PCB
